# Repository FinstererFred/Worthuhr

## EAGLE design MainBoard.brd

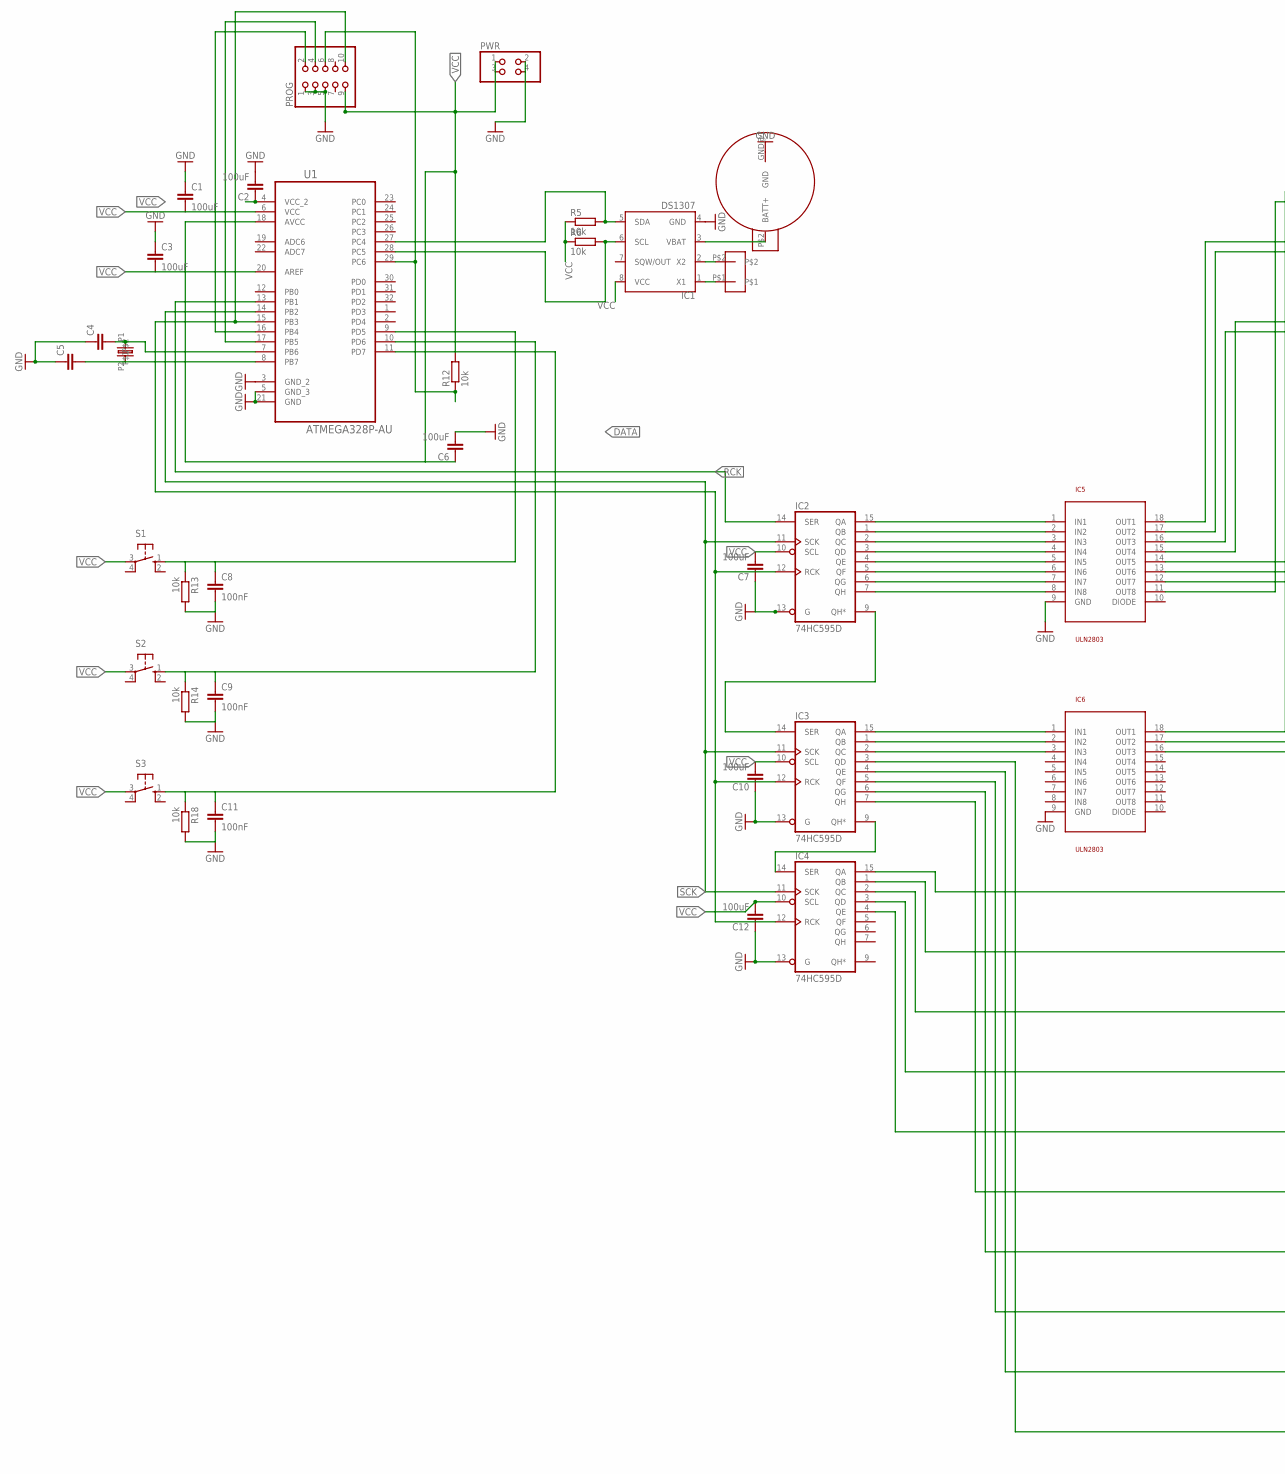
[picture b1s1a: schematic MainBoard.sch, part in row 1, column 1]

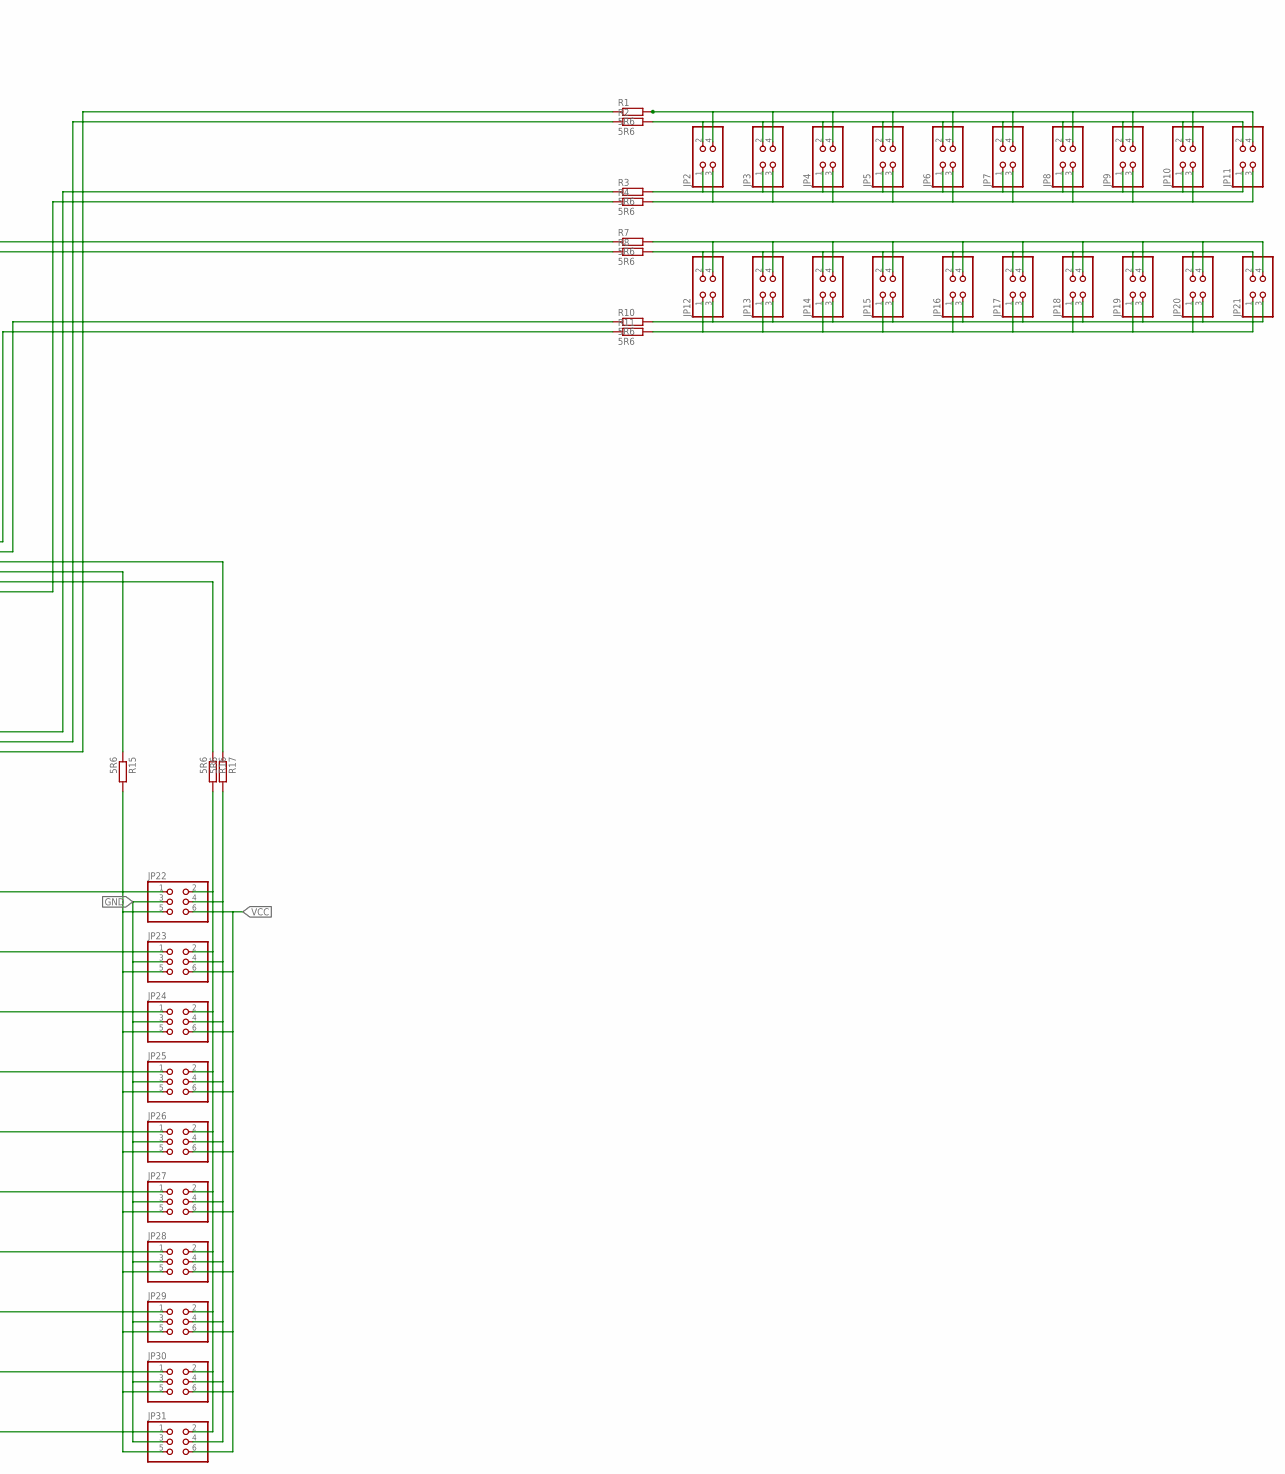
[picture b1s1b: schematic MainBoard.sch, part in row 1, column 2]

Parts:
C1, C2, C3, C6, C7, C10, C12: 100uF; C0603
C4, C5: C-EUC0603; C0603
C8, C9, C11: 100nF; C0603
IC1: DS1307; SOIC-8
IC2, IC3, IC4: 74HC595D; SO16
IC5, IC6: ULN2803; SO18L
JP2, JP3, JP4, JP5, JP6, JP7, JP8, JP9, JP10, JP11, JP12, JP13, JP14, JP15, JP16, JP17, JP18, JP19, JP20, JP21: PINHD-2X2; 2X02
JP22, JP23, JP24, JP25, JP26, JP27, JP28, JP29, JP30, JP31: PINHD-2X3; 2X03
PROG: PINHD-2X5; 2X05
PWR: PINHD-2X2; 2X02
R1, R2, R3, R4, R7, R8, R10, R11, R15, R16, R17: 5R6; R0805
R5, R6, R12, R13, R14, R18: 10k; R0603
S1, S2, S3: 10-XX; B3F-10XX
U1: ATMEGA328P-AU; QFP80P900X900X120-32N
U$1: CR2032; CR2023
U$2: CC5V-T1A
U$3: 16,00-MT

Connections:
DATA: IC2.14 (SER), U1.13 (PB1)
GND: C1.1, C2.2, C3.1, C4.1, C5.1, C6.2, C7.1, C8.2, C9.2, C10.1, C11.2, C12.1, IC1.4 (GND), IC2.8 (GND), IC2.13 (G), IC3.8 (GND), IC3.13 (G), IC4.8 (GND), IC4.13 (G), IC5.9 (GND), IC6.9 (GND), JP22.3, JP23.3, JP24.3, JP25.3, JP26.3, JP27.3, JP28.3, JP29.3, JP30.3, JP31.3, PROG.1, PROG.3, PROG.5, PWR.2, PWR.4, R13.2, R14.2, R18.2, U1.3 (GND_2), U1.5 (GND_3), U1.21 (GND), U$1.GND@1 (GND)
unnamed: IC5.16 (OUT3), R11.1
unnamed: IC5.12 (OUT7), R16.1
unnamed: JP22.2, JP23.2, JP24.2, JP25.2, JP26.2, JP27.2, JP28.2, JP29.2, JP30.2, JP31.2, R16.2
unnamed: IC1.2 (X2), U$2.P$2
unnamed: PROG.6, R12.1, U1.29 (PC6)
unnamed: IC5.13 (OUT6), R15.1
unnamed: C8.1, R13.1, S1.1 (S), U1.9 (PD5)
unnamed: IC5.14 (OUT5), R17.1
unnamed: IC3.9 (QH*), IC4.14 (SER)
unnamed: IC2.9 (QH*), IC3.14 (SER)
unnamed: IC5.18 (OUT1), R7.1
unnamed: PROG.2, U1.16 (PB4)
unnamed: IC2.15 (QA), IC5.1 (IN1)
unnamed: C9.1, R14.1, S2.1 (S), U1.10 (PD6)
unnamed: C11.1, R18.1, S3.1 (S), U1.11 (PD7)
unnamed: IC1.1 (X1), U$2.P$1
unnamed: C5.2, U1.8 (PB7), U$3.P2
unnamed: IC2.1 (QB), IC5.2 (IN2)
unnamed: IC2.2 (QC), IC5.3 (IN3)
unnamed: IC2.3 (QD), IC5.4 (IN4)
unnamed: IC6.18 (OUT1), R3.1
unnamed: IC6.17 (OUT2), R2.1
unnamed: IC6.16 (OUT3), R1.1
unnamed: IC2.4 (QE), IC5.5 (IN5)
unnamed: IC3.3 (QD), JP31.1
unnamed: IC1.3 (VBAT), U$1.P$2 (BATT+)
unnamed: PROG.4, U1.17 (PB5)
unnamed: IC1.5 (SDA), R5.2, U1.27 (PC4)
unnamed: IC2.5 (QF), IC5.6 (IN6)
unnamed: IC2.6 (QG), IC5.7 (IN7)
unnamed: IC4.15 (QA), JP22.1
unnamed: IC1.6 (SCL), R6.2, U1.28 (PC5)
unnamed: IC4.1 (QB), JP23.1
unnamed: IC2.7 (QH), IC5.8 (IN8)
unnamed: C4.2, U1.7 (PB6), U$3.P1
unnamed: IC3.15 (QA), IC6.1 (IN1)
unnamed: JP12.1, JP13.1, JP14.1, JP15.1, JP16.1, JP17.1, JP18.1, JP19.1, JP20.1, JP21.1, R11.2
unnamed: IC3.1 (QB), IC6.2 (IN2)
unnamed: IC3.2 (QC), IC6.3 (IN3)
unnamed: IC5.15 (OUT4), R10.1
unnamed: JP12.3, JP13.3, JP14.3, JP15.3, JP16.3, JP17.3, JP18.3, JP19.3, JP20.3, JP21.3, R10.2
unnamed: JP22.5, JP23.5, JP24.5, JP25.5, JP26.5, JP27.5, JP28.5, JP29.5, JP30.5, JP31.5, R15.2
unnamed: IC5.11 (OUT8), R4.1
unnamed: IC5.17 (OUT2), R8.1
unnamed: IC4.2 (QC), JP24.1
unnamed: IC4.3 (QD), JP25.1
unnamed: IC4.4 (QE), JP26.1
unnamed: IC3.7 (QH), JP27.1
unnamed: IC3.6 (QG), JP28.1
unnamed: IC3.5 (QF), JP29.1
unnamed: IC3.4 (QE), JP30.1
unnamed: JP2.1, JP3.1, JP4.1, JP5.1, JP6.1, JP7.1, JP8.1, JP9.1, JP10.1, JP11.1, R3.2
unnamed: JP22.4, JP23.4, JP24.4, JP25.4, JP26.4, JP27.4, JP28.4, JP29.4, JP30.4, JP31.4, R17.2
unnamed: JP2.3, JP3.3, JP4.3, JP5.3, JP6.3, JP7.3, JP8.3, JP9.3, JP10.3, JP11.3, R4.2
unnamed: JP2.2, JP3.2, JP4.2, JP5.2, JP6.2, JP7.2, JP8.2, JP9.2, JP10.2, JP11.2, R2.2
unnamed: JP2.4, JP3.4, JP4.4, JP5.4, JP6.4, JP7.4, JP8.4, JP9.4, JP10.4, JP11.4, R1.2
unnamed: JP12.2, JP13.2, JP14.2, JP15.2, JP16.2, JP17.2, JP18.2, JP19.2, JP20.2, JP21.2, R8.2
unnamed: JP12.4, JP13.4, JP14.4, JP15.4, JP16.4, JP17.4, JP18.4, JP19.4, JP20.4, JP21.4, R7.2
RCK: IC2.12 (RCK), IC3.12 (RCK), IC4.12 (RCK), PROG.10, U1.15 (PB3)
SCK: IC2.11 (SCK), IC3.11 (SCK), IC4.11 (SCK), U1.14 (PB2)
VCC: C1.2, C2.1, C3.2, C6.1, C7.2, C10.2, C12.2, IC1.8 (VCC), IC2.10 (SCL), IC2.16 (VCC), IC3.10 (SCL), IC3.16 (VCC), IC4.10 (SCL), IC4.16 (VCC), JP22.6, JP23.6, JP24.6, JP25.6, JP26.6, JP27.6, JP28.6, JP29.6, JP30.6, JP31.6, PROG.9, PWR.1, PWR.3, R5.1, R6.1, R12.2, S1.3, S2.3, S3.3, U1.4 (VCC_2), U1.6 (VCC), U1.18 (AVCC), U1.20 (AREF)

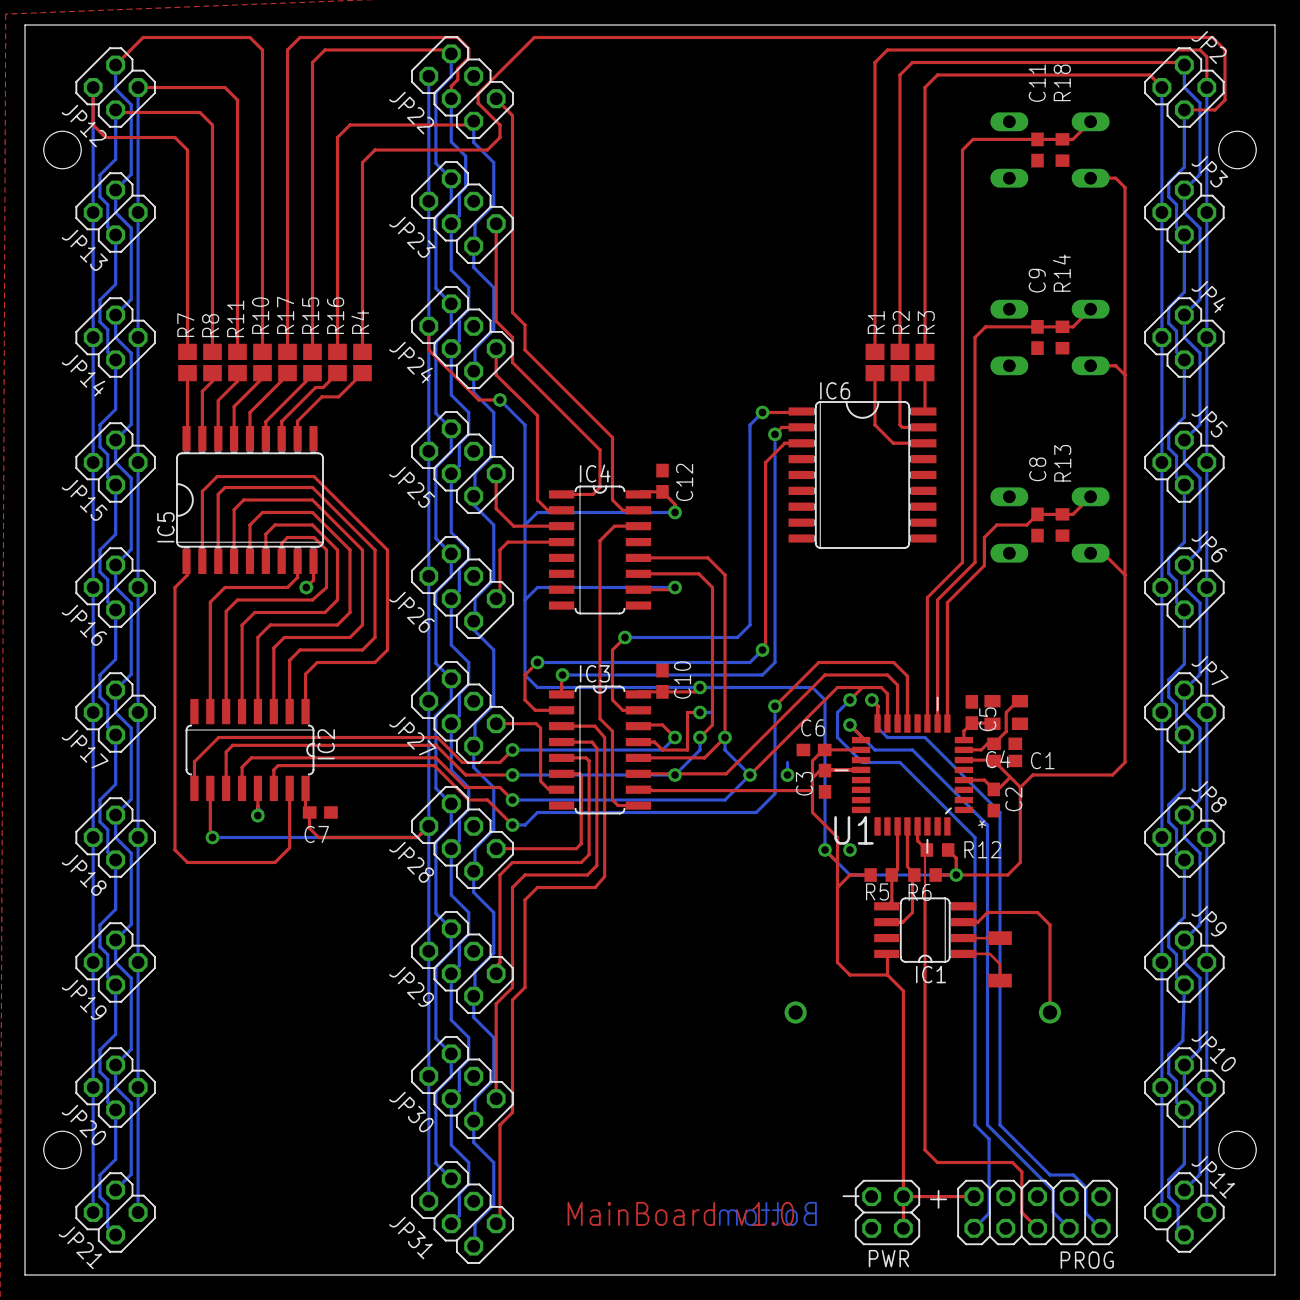
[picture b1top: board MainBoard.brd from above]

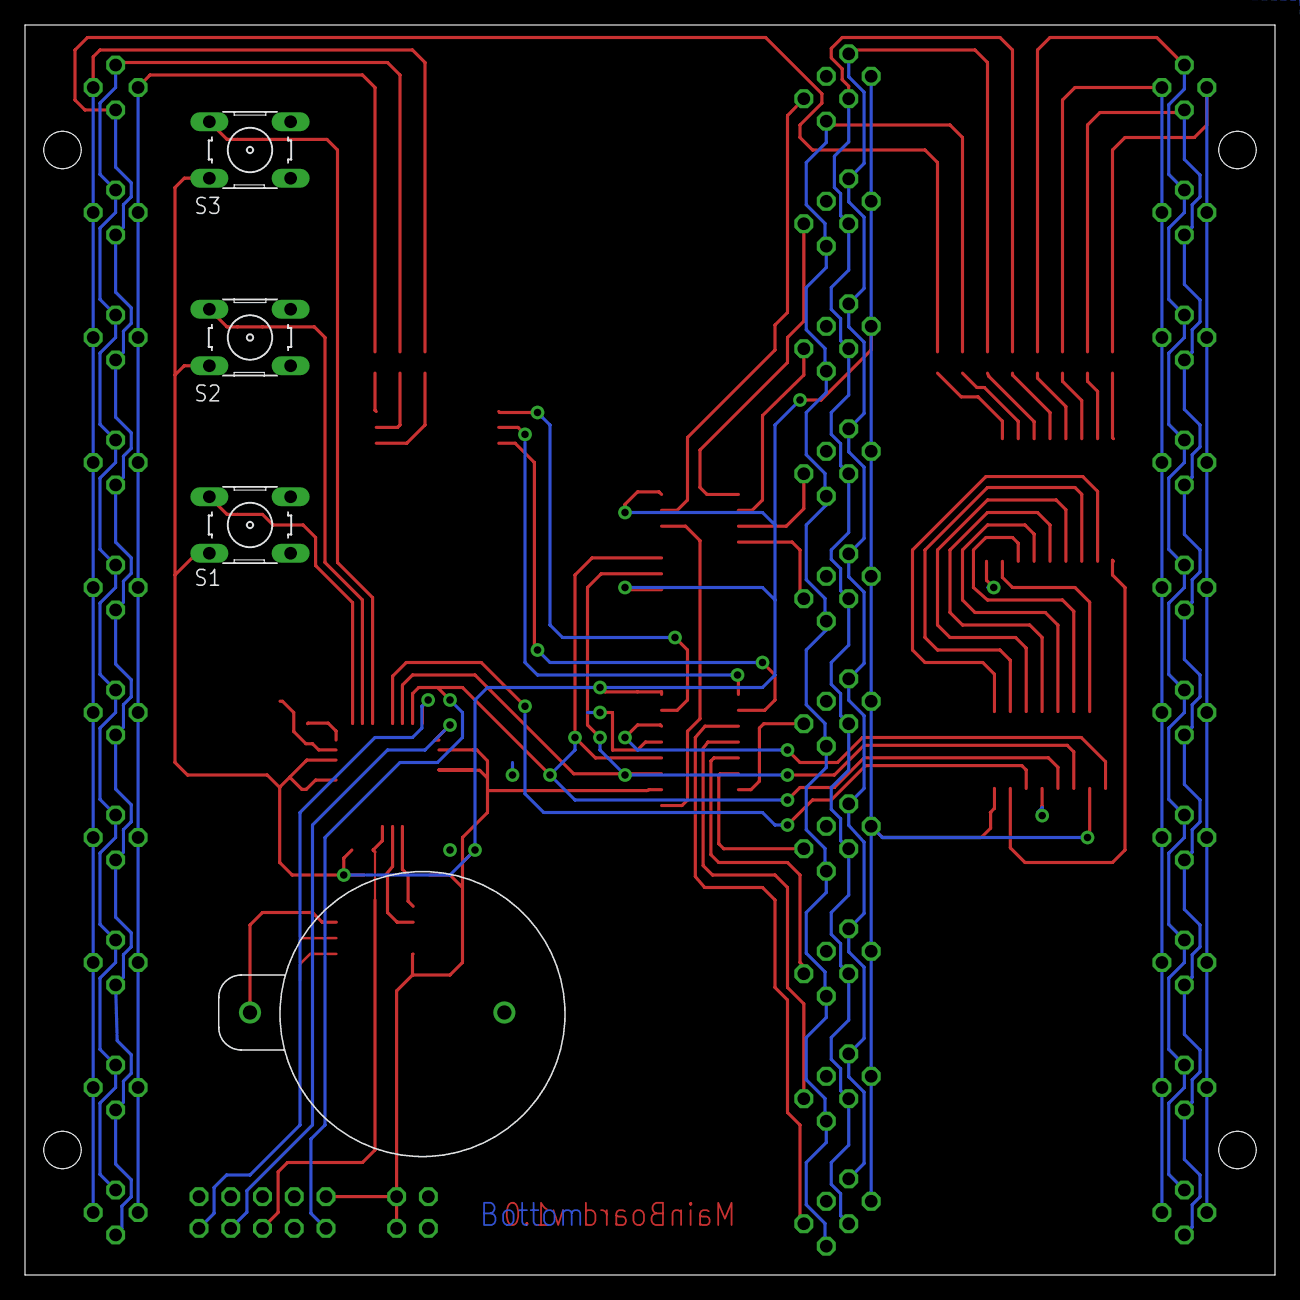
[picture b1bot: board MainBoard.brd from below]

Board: 4 copper layers, 100.0 x 100.0 mm, 74 parts (4 on the bottom side), 63 nets.

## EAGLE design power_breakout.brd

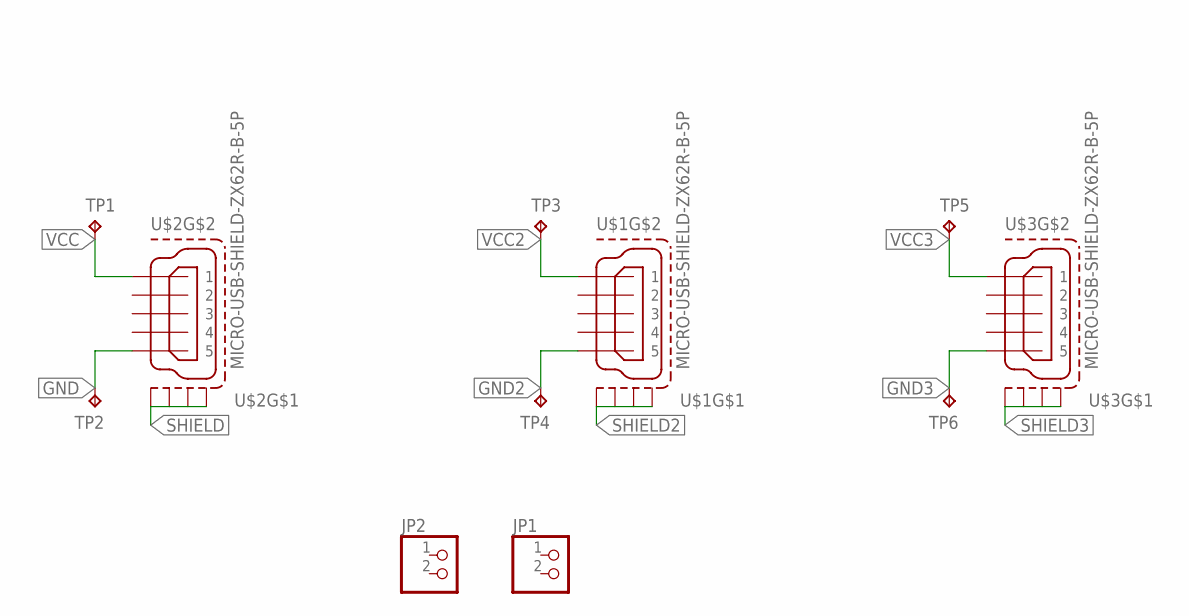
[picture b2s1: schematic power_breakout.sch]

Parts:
JP1, JP2: PINHD-1X2/90; 1X02/90
TP1, TP2, TP3, TP4, TP5, TP6: TPB1,27; B1,27
U$1, U$2, U$3: MICRO-USB-SHIELD-ZX62R-B-5P; ZX62R-B-5P

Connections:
GND: TP2.TP, U$2.5
GND2: TP4.TP, U$1.5
GND3: TP6.TP, U$3.5
SHIELD: U$2.M1 (S1), U$2.M2 (S2), U$2.M3 (S3), U$2.M4 (S4)
SHIELD2: U$1.M1 (S1), U$1.M2 (S2), U$1.M3 (S3), U$1.M4 (S4)
SHIELD3: U$3.M1 (S1), U$3.M2 (S2), U$3.M3 (S3), U$3.M4 (S4)
VCC: TP1.TP, U$2.1
VCC2: TP3.TP, U$1.1
VCC3: TP5.TP, U$3.1

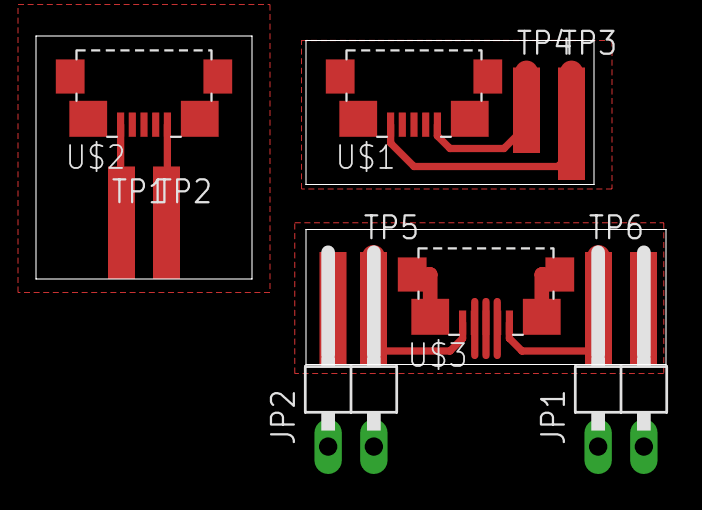
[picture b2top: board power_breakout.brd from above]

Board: 2 copper layers, 35.0 x 18.2 mm, 11 parts (0 on the bottom side), 9 nets.

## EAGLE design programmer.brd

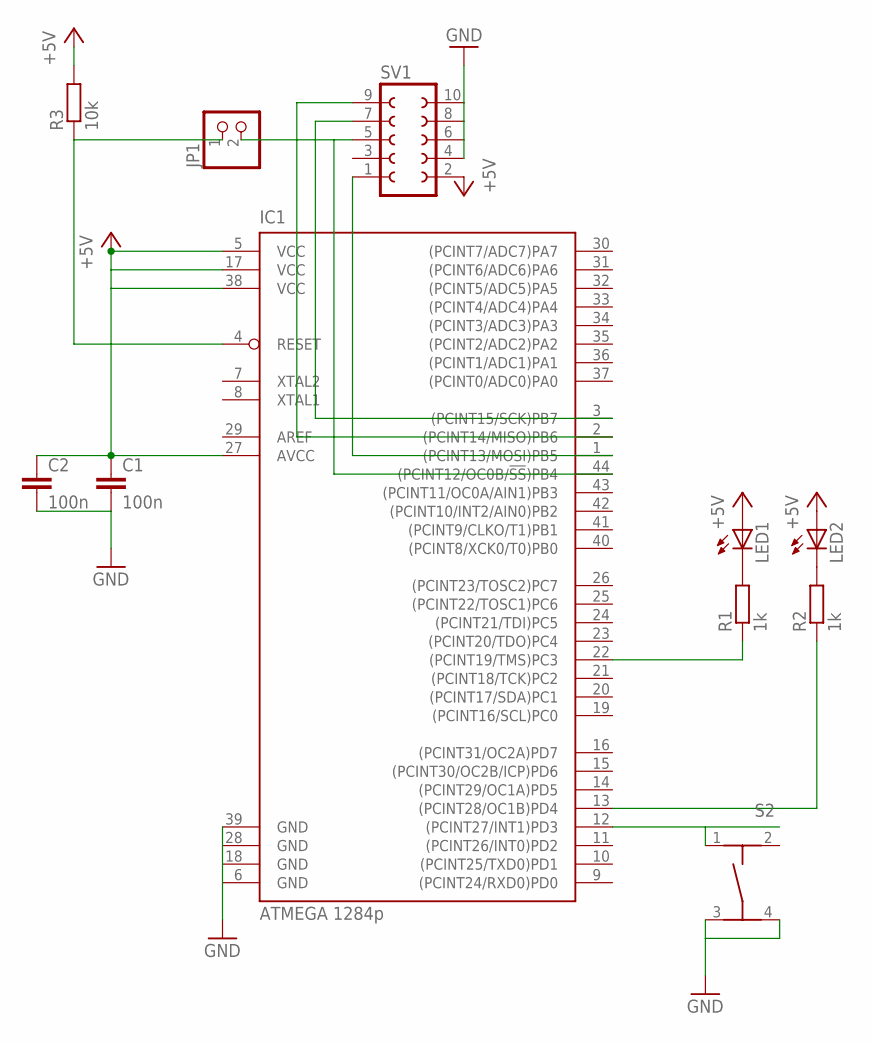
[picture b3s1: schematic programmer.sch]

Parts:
C1, C2: 100n; C0603
IC1: ATMEGA 1284p; TQFP44
JP1: PINHD-1X2; 1X02
LED1, LED2: LED; SMARTLED-TTW
R1, R2: 1k; R0603
R3: 10k; R0603
S2: TASTER-9314_SMD
SV1: FE05-2W

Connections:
+5V: C1.1, C2.1, IC1.5 (VCC), IC1.17 (VCC), IC1.27 (AVCC), IC1.38 (VCC), LED1.A@1 (A), LED2.A@1 (A), R3.2, SV1.2
GND: C1.2, C2.2, IC1.6 (GND), IC1.18 (GND), IC1.28 (GND), IC1.39 (GND), S2.3, S2.4, SV1.4, SV1.6, SV1.8, SV1.10
unnamed: IC1.4 (RESET), JP1.1, R3.1
unnamed: IC1.44 ((PCINT12/OC0B/!SS!)PB4), JP1.2, SV1.5
unnamed: LED1.C@1 (C), R1.2
unnamed: LED2.C@1 (C), R2.2
unnamed: IC1.3 ((PCINT15/SCK)PB7), SV1.7
unnamed: IC1.1 ((PCINT13/MOSI)PB5), SV1.1
unnamed: IC1.2 ((PCINT14/MISO)PB6), SV1.9
unnamed: IC1.12 ((PCINT27/INT1)PD3), S2.1
unnamed: IC1.22 ((PCINT19/TMS)PC3), R1.1
unnamed: IC1.13 ((PCINT28/OC1B)PD4), R2.1

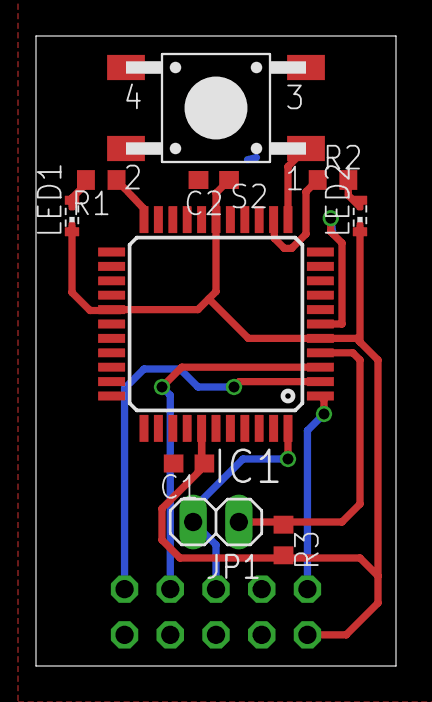
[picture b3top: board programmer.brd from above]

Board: 2 copper layers, 20.0 x 35.0 mm, 11 parts (1 on the bottom side), 12 nets.

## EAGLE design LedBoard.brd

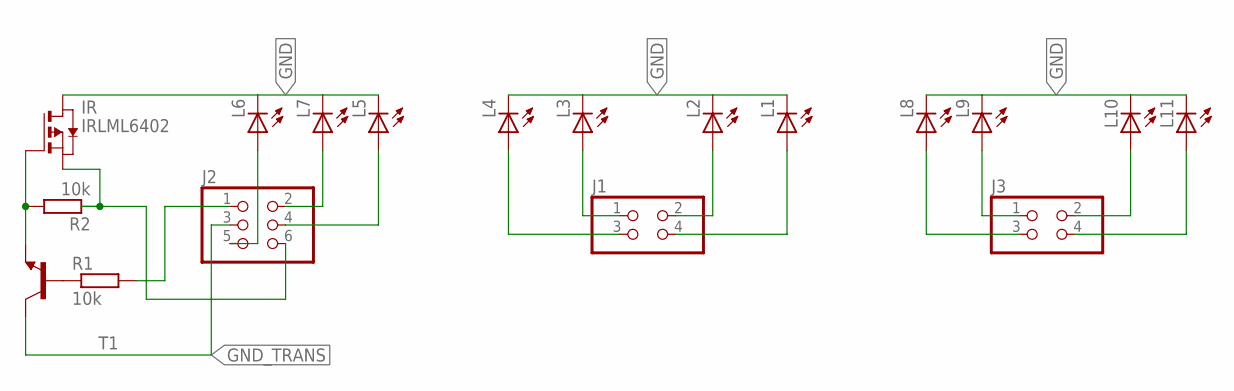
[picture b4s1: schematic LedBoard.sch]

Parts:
IR: IRLML6402; SOT-23
J1, J3: PINHD-2X2; 2X02
J2: PINHD-2X3; 2X03
L1, L2, L3, L4, L5, L6, L7, L8, L9, L10, L11: LEDKA-3528ASYC; KA-3528ASYC
R1, R2: 10k; R1206
T1: BC818-40-NPN-SOT23-BEC; SOT23-BEC

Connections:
GND: IR.3 (D), L1.C, L2.C, L3.C, L4.C, L5.C, L6.C, L7.C, L8.C, L9.C, L10.C, L11.C
GND_TRANS: J2.3, T1.C
unnamed: J1.4, L1.A
unnamed: IR.1 (G), R2.2, T1.E
unnamed: J1.2, L2.A
unnamed: J1.1, L3.A
unnamed: J1.3, L4.A
unnamed: J2.4, L5.A
unnamed: J2.5, L6.A
unnamed: J3.4, L11.A
unnamed: IR.2 (S), J2.6, R2.1
unnamed: R1.1, T1.B
unnamed: J3.2, L10.A
unnamed: J3.1, L9.A
unnamed: J3.3, L8.A
unnamed: J2.2, L7.A
unnamed: J2.1, R1.2

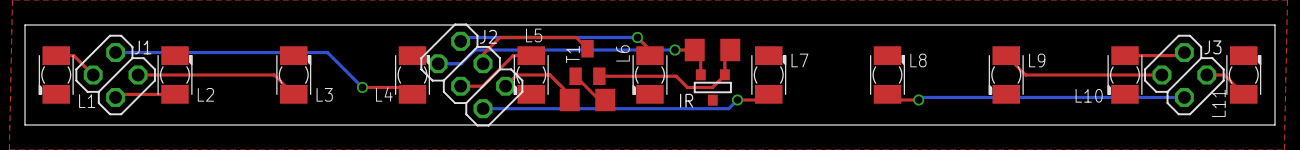
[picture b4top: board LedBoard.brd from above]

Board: 2 copper layers, 100.0 x 8.0 mm, 18 parts (0 on the bottom side), 17 nets.

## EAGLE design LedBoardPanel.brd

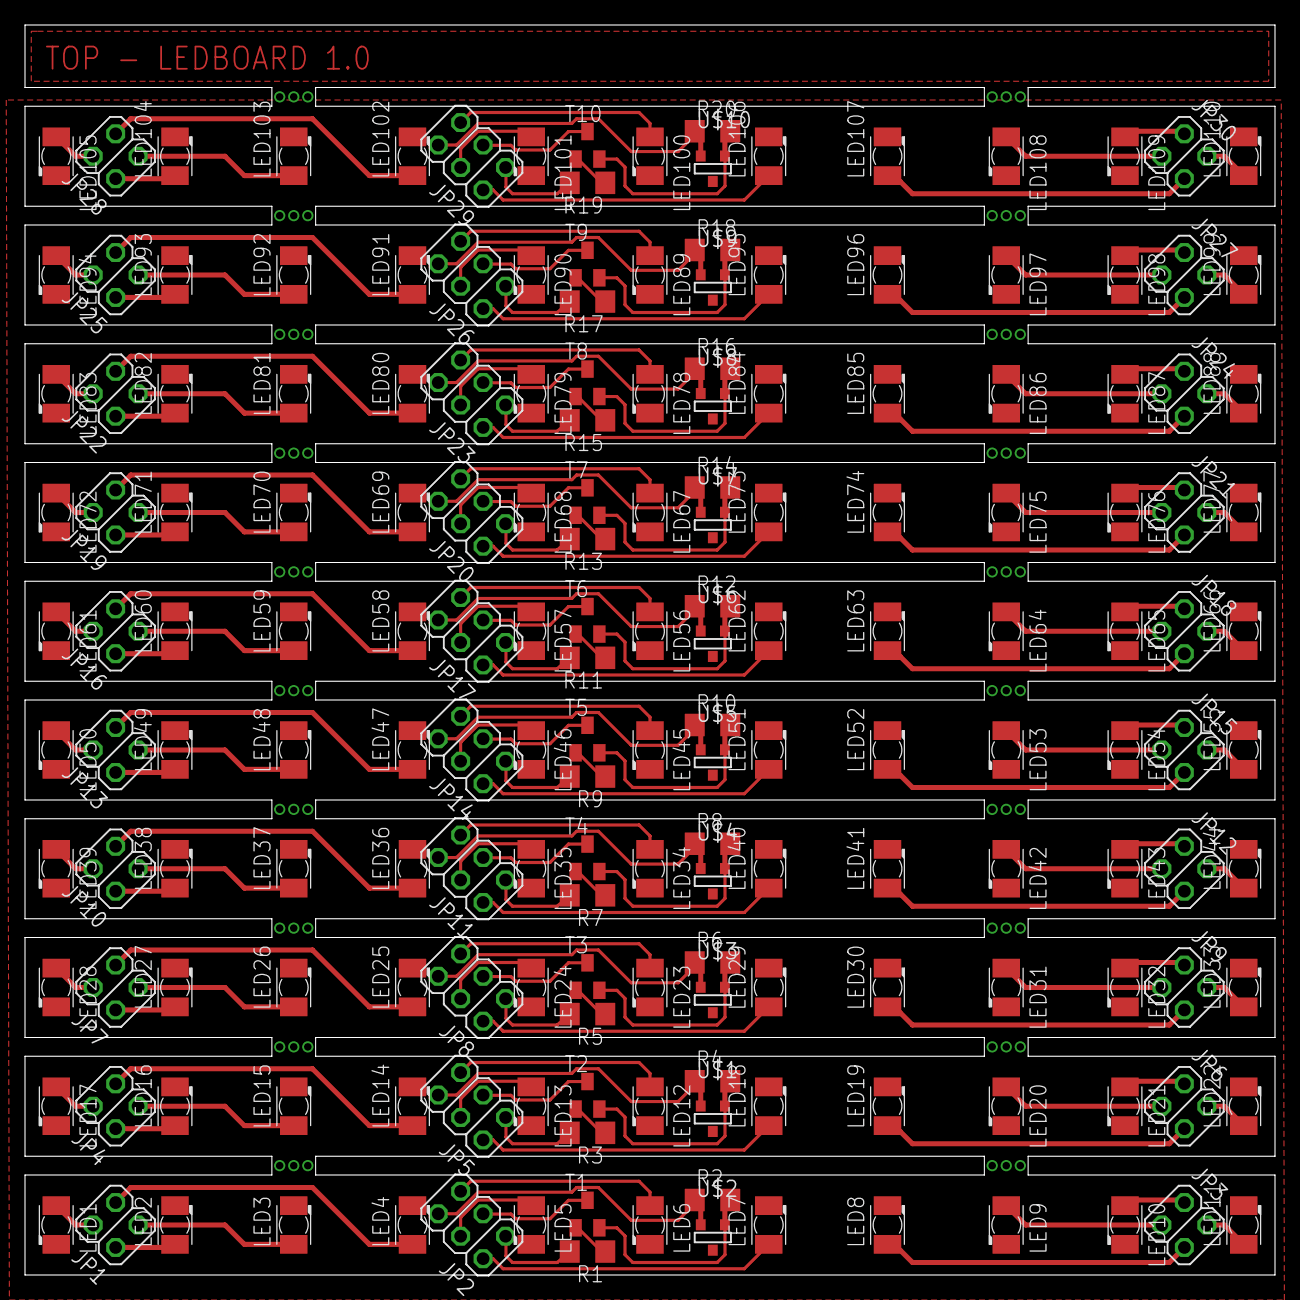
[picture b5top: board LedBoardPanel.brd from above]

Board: 2 copper layers, 100.0 x 100.0 mm, 180 parts (0 on the bottom side), 161 nets.

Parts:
JP1, JP3, JP4, JP6, JP7, JP9, JP10, JP12, JP13, JP15, JP16, JP18, JP19, JP21, JP22, JP24, JP25, JP27, JP28, JP30: 2X02
JP2, JP5, JP8, JP11, JP14, JP17, JP20, JP23, JP26, JP29: 2X03
LED1, LED2, LED3, LED4, LED5, LED6, LED7, LED8, LED9, LED10, LED11, LED12, LED13, LED14, LED15, LED16, LED17, LED18, LED19, LED20, LED21, LED22, LED23, LED24, LED25, LED26, LED27, LED28, LED29, LED30, LED31, LED32, LED33, LED34, LED35, LED36, LED37, LED38, LED39, LED40, LED41, LED42, LED43, LED44, LED45, LED46, LED47, LED48, LED49, LED50, LED51, LED52, LED53, LED54, LED55, LED56, LED57, LED58, LED59, LED60, LED61, LED62, LED63, LED64, LED65, LED66, LED67, LED68, LED69, LED70, LED71, LED72, LED73, LED74, LED75, LED76, LED77, LED78, LED79, LED80, LED81, LED82, LED83, LED84, LED85, LED86, LED87, LED88, LED89, LED90, LED91, LED92, LED93, LED94, LED95, LED96, LED97, LED98, LED99, LED100, LED101, LED102, LED103, LED104, LED105, LED106, LED107, LED108, LED109, LED110: KA-3528ASYC
R1, R2, R3, R4, R5, R6, R7, R8, R9, R10, R11, R12, R13, R14, R15, R16, R17, R18, R19, R20: 10k; R1206
T1, T2, T3, T4, T5, T6, T7, T8, T9, T10: SOT23-BEC
U$1, U$2, U$3, U$4, U$5, U$6, U$7, U$8, U$9, U$10: IRLML6402; SOT-23

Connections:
GND: LED1.C, LED2.C, LED3.C, LED4.C, LED5.C, LED6.C, LED7.C, LED8.C, LED9.C, LED10.C, LED11.C, LED12.C, LED13.C, LED14.C, LED15.C, LED16.C, LED17.C, LED18.C, LED19.C, LED20.C, LED21.C, LED22.C, LED23.C, LED24.C, LED25.C, LED26.C, LED27.C, LED28.C, LED29.C, LED30.C, LED31.C, LED32.C, LED33.C, LED34.C, LED35.C, LED36.C, LED37.C, LED38.C, LED39.C, LED40.C, LED41.C, LED42.C, LED43.C, LED44.C, LED45.C, LED46.C, LED47.C, LED48.C, LED49.C, LED50.C, LED51.C, LED52.C, LED53.C, LED54.C, LED55.C, LED56.C, LED57.C, LED58.C, LED59.C, LED60.C, LED61.C, LED62.C, LED63.C, LED64.C, LED65.C, LED66.C, LED67.C, LED68.C, LED69.C, LED70.C, LED71.C, LED72.C, LED73.C, LED74.C, LED75.C, LED76.C, LED77.C, LED78.C, LED79.C, LED80.C, LED81.C, LED82.C, LED83.C, LED84.C, LED85.C, LED86.C, LED87.C, LED88.C, LED89.C, LED90.C, LED91.C, LED92.C, LED93.C, LED94.C, LED95.C, LED96.C, LED97.C, LED98.C, LED99.C, LED100.C, LED101.C, LED102.C, LED103.C, LED104.C, LED105.C, LED106.C, LED107.C, LED108.C, LED109.C, LED110.C, U$1.3, U$2.3, U$3.3, U$4.3, U$5.3, U$6.3, U$7.3, U$8.3, U$9.3, U$10.3
GND_TRANS: JP2.3, T1.C
GND_TRANS1: JP5.3, T2.C
GND_TRANS2: JP8.3, T3.C
GND_TRANS3: JP11.3, T4.C
GND_TRANS4: JP14.3, T5.C
GND_TRANS5: JP17.3, T6.C
GND_TRANS6: JP20.3, T7.C
GND_TRANS7: JP23.3, T8.C
GND_TRANS8: JP26.3, T9.C
GND_TRANS9: JP29.3, T10.C
unnamed: JP1.4, LED1.A
unnamed: R2.2, T1.E, U$2.1
unnamed: JP1.2, LED2.A
unnamed: JP1.1, LED3.A
unnamed: JP1.3, LED4.A
unnamed: JP2.4, LED5.A
unnamed: JP2.5, LED6.A
unnamed: JP3.4, LED11.A
unnamed: JP2.6, R2.1, U$2.2
unnamed: R1.1, T1.B
unnamed: JP3.2, LED10.A
unnamed: JP3.1, LED9.A
unnamed: JP3.3, LED8.A
unnamed: JP2.2, LED7.A
unnamed: JP2.1, R1.2
unnamed: R4.2, T2.E, U$1.1
unnamed: R3.1, T2.B
unnamed: JP5.1, R3.2
unnamed: JP5.6, R4.1, U$1.2
unnamed: JP4.4, LED17.A
unnamed: JP4.2, LED16.A
unnamed: JP4.1, LED15.A
unnamed: JP4.3, LED14.A
unnamed: JP5.4, LED13.A
unnamed: JP5.5, LED12.A
unnamed: JP6.4, LED22.A
unnamed: JP6.2, LED21.A
unnamed: JP6.1, LED20.A
unnamed: JP6.3, LED19.A
unnamed: JP5.2, LED18.A
unnamed: R6.2, T3.E, U$3.1
unnamed: R5.1, T3.B
unnamed: JP8.1, R5.2
unnamed: JP8.6, R6.1, U$3.2
unnamed: JP7.4, LED28.A
unnamed: JP7.2, LED27.A
unnamed: JP7.1, LED26.A
unnamed: JP7.3, LED25.A
unnamed: JP8.4, LED24.A
unnamed: JP8.5, LED23.A
unnamed: JP9.4, LED33.A
unnamed: JP9.2, LED32.A
unnamed: JP9.1, LED31.A
unnamed: JP9.3, LED30.A
unnamed: JP8.2, LED29.A
unnamed: R8.2, T4.E, U$4.1
unnamed: R7.1, T4.B
unnamed: JP11.1, R7.2
unnamed: JP11.6, R8.1, U$4.2
unnamed: JP10.4, LED39.A
unnamed: JP10.2, LED38.A
unnamed: JP10.1, LED37.A
unnamed: JP10.3, LED36.A
unnamed: JP11.4, LED35.A
unnamed: JP11.5, LED34.A
unnamed: JP12.4, LED44.A
unnamed: JP12.2, LED43.A
unnamed: JP12.1, LED42.A
unnamed: JP12.3, LED41.A
unnamed: JP11.2, LED40.A
unnamed: R10.2, T5.E, U$5.1
unnamed: R9.1, T5.B
unnamed: JP14.1, R9.2
unnamed: JP14.6, R10.1, U$5.2
unnamed: JP13.4, LED50.A
unnamed: JP13.2, LED49.A
unnamed: JP13.1, LED48.A
unnamed: JP13.3, LED47.A
unnamed: JP14.4, LED46.A
unnamed: JP14.5, LED45.A
unnamed: JP15.4, LED55.A
unnamed: JP15.2, LED54.A
unnamed: JP15.1, LED53.A
unnamed: JP15.3, LED52.A
unnamed: JP14.2, LED51.A
unnamed: R12.2, T6.E, U$6.1
unnamed: R11.1, T6.B
unnamed: JP17.1, R11.2
unnamed: JP17.6, R12.1, U$6.2
unnamed: JP16.4, LED61.A
unnamed: JP16.2, LED60.A
unnamed: JP16.1, LED59.A
unnamed: JP16.3, LED58.A
unnamed: JP17.4, LED57.A
unnamed: JP17.5, LED56.A
unnamed: JP18.4, LED66.A
unnamed: JP18.2, LED65.A
unnamed: JP18.1, LED64.A
unnamed: JP18.3, LED63.A
unnamed: JP17.2, LED62.A
unnamed: R14.2, T7.E, U$7.1
unnamed: R13.1, T7.B
unnamed: JP20.1, R13.2
unnamed: JP20.6, R14.1, U$7.2
unnamed: JP19.4, LED72.A
unnamed: JP19.2, LED71.A
unnamed: JP19.1, LED70.A
unnamed: JP19.3, LED69.A
unnamed: JP20.4, LED68.A
unnamed: JP20.5, LED67.A
unnamed: JP21.4, LED77.A
unnamed: JP21.2, LED76.A
unnamed: JP21.1, LED75.A
unnamed: JP21.3, LED74.A
unnamed: JP20.2, LED73.A
unnamed: R16.2, T8.E, U$8.1
unnamed: R15.1, T8.B
unnamed: JP23.1, R15.2
unnamed: JP23.6, R16.1, U$8.2
unnamed: JP22.4, LED83.A
unnamed: JP22.2, LED82.A
unnamed: JP22.1, LED81.A
unnamed: JP22.3, LED80.A
unnamed: JP23.4, LED79.A
unnamed: JP23.5, LED78.A
unnamed: JP24.4, LED88.A
unnamed: JP24.2, LED87.A
unnamed: JP24.1, LED86.A
unnamed: JP24.3, LED85.A
unnamed: JP23.2, LED84.A
unnamed: R18.2, T9.E, U$9.1
unnamed: R17.1, T9.B
unnamed: JP26.1, R17.2
unnamed: JP26.6, R18.1, U$9.2
unnamed: JP25.4, LED94.A
unnamed: JP25.2, LED93.A
unnamed: JP25.1, LED92.A
unnamed: JP25.3, LED91.A
unnamed: JP26.4, LED90.A
unnamed: JP26.5, LED89.A
unnamed: JP27.4, LED99.A
unnamed: JP27.2, LED98.A
unnamed: JP27.1, LED97.A
unnamed: JP27.3, LED96.A
unnamed: JP26.2, LED95.A
unnamed: R20.2, T10.E, U$10.1
unnamed: R19.1, T10.B
unnamed: JP29.1, R19.2
unnamed: JP29.6, R20.1, U$10.2
unnamed: JP28.4, LED105.A
unnamed: JP28.2, LED104.A
unnamed: JP28.1, LED103.A
unnamed: JP28.3, LED102.A
unnamed: JP29.4, LED101.A
unnamed: JP29.5, LED100.A
unnamed: JP30.4, LED110.A
unnamed: JP30.2, LED109.A
unnamed: JP30.1, LED108.A
unnamed: JP30.3, LED107.A
unnamed: JP29.2, LED106.A

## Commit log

2015-12-11 - Added 3 Buttons - Organized Schematic
2015-12-12 Finished Routing an Panelizing
2015-12-21 Changed tolerances on ledboard and mainboard
2015-12-21 Finalizing prototype
2015-12-23 Added power breakout board and ISPnub (http://www.fischl.de/ispnub/) board
2015-12-31 Final layout of prototype
